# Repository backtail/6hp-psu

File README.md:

# 6hp psu
6HP Eurorack module

### Render

### Input
- 15V-20V
- 2.1/5.5mm Barrel Jack 
- use a *USB PD Trigger Adapter* i.e. to use a power bank

### Output
Without a heatsink
* +5V @ 1.5A
* +12V @ 1A
* -12V @ 1A

Not tested with a heatsink yet. Potentially up to 2..2.5A
per rail! *(Depending on heatsink dimensions and rack depth)*

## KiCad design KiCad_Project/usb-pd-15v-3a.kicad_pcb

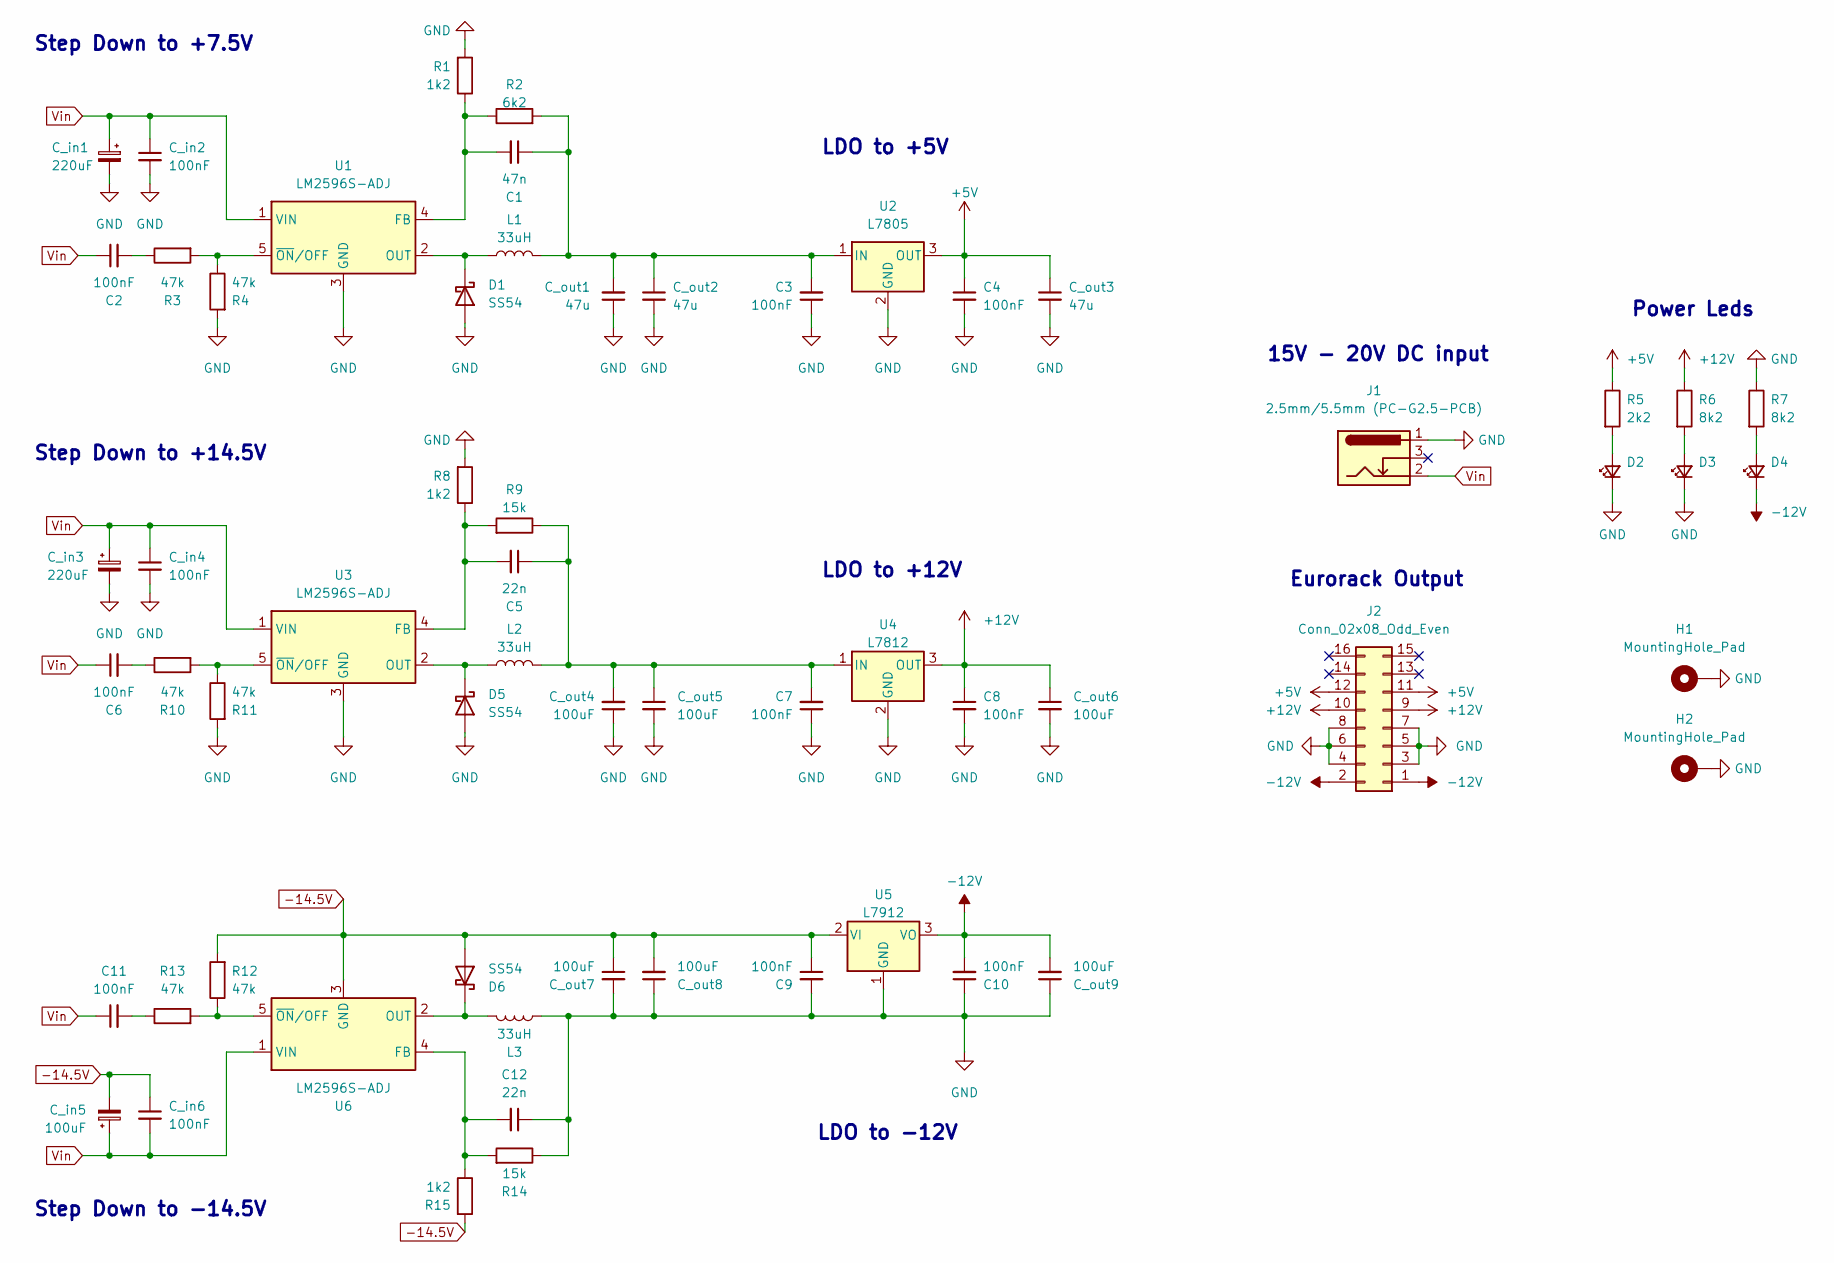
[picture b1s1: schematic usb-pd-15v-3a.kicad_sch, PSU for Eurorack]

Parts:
C1: 47n; C_0603_1608Metric; JLCPCB Reference C1622
C2, C3, C4, C6, C7, C8, C9, C10, C11: 100nF; C_0805_2012Metric; JLCPCB Reference C49678
C5, C12: 22n; C_0603_1608Metric; JLCPCB Reference C21122
C_in1, C_in3: 220uF; CP_Elec_10x7.7; JLCPCB Reference C249881
C_in2, C_in4, C_in6: 100nF; C_1206_3216Metric; JLCPCB Reference C24497
C_in5: 100uF; CP_Elec_6.3x7.7; JLCPCB Reference C165974
C_out1, C_out2, C_out3: 47u; C_1206_3216Metric; JLCPCB Reference C96123
C_out4, C_out5, C_out6, C_out7, C_out8, C_out9: 100uF; L_1210_3225Metric; JLCPCB Reference C90143
D1, D5, D6: SS54; D_SMA; JLCPCB Reference C22452
D2, D3, D4: LED_D3.0mm
H1, H2: MountingHole_Pad; MountingHole_3.2mm_M3_Pad_TopOnly
J1: 2.5mm/5.5mm (PC-G2.5-PCB); DC_Barrel_Jack_2.5mm_5.7mm_Verrtical
J2: Conn_02x08_Odd_Even; IDC-Header_2x08_P2.54mm_Vertical
L1, L2, L3: 33uH; L_12x12mm_H8mm; JLCPCB Reference C718306
R1, R8, R15: 1k2; R_0805_2012Metric_Pad1.20x1.40mm_HandSolder; JLCPCB Reference C17379
R2: 6k2; R_0805_2012Metric_Pad1.20x1.40mm_HandSolder; JLCPCB Reference C17767
R3, R4, R10, R11, R12, R13: 47k; R_0603_1608Metric; JLCPCB Reference C25819
R5: 2k2; R_0603_1608Metric; JLCPCB Reference C4190
R6, R7: 8k2; R_0603_1608Metric; JLCPCB Reference C25981
R9, R14: 15k; R_0805_2012Metric_Pad1.20x1.40mm_HandSolder; JLCPCB Reference C17475
U1, U3, U6: LM2596S-ADJ; TO-263-5_TabPin3; JLCPCB Reference C347423
U2: L7805; TO-263-3_TabPin2; JLCPCB Reference C507146
U4: L7812; TO-263-3_TabPin2; JLCPCB Reference C507140
U5: L7912; TO-263-3_TabPin2; JLCPCB Reference C2926383

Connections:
+5V: C4.1, C_out3.1, J2.11, J2.12, R5.1, U2.3 (OUT)
+12V: C8.1, C_out6.1, J2.9, J2.10, R6.1, U4.3 (OUT)
-12V: C10.2, C_out9.2, D4.1 (K), J2.1, J2.2, U5.3 (VO)
-14.5V: C9.1, C_in5.2, C_in6.1, C_out7.1, C_out8.2, D6.2 (A), R12.2, R15.2, U5.2 (VI), U6.3 (GND)
GND: C3.1, C4.2, C7.1, C8.2, C9.2, C10.1, C12.1, C_in1.2, C_in2.2, C_in3.2, C_in4.2, C_out1.1, C_out2.2, C_out3.2, C_out4.1, C_out5.2, C_out6.2, C_out7.2, C_out8.1, C_out9.1, D1.2 (A), D2.1 (K), D3.1 (K), D5.2 (A), H1.1, H2.1, J1.1, J2.3, J2.4, J2.5, J2.6, J2.7, J2.8, L3.1, R1.2, R4.2, R7.1, R8.2, R11.2, R14.1, U1.3 (GND), U2.2 (GND), U3.3 (GND), U4.2 (GND), U5.1 (GND)
unnamed: C1.1, C3.2, C_out1.2, C_out2.1, L1.2, R2.2, U2.1 (IN)
unnamed: C1.2, R1.1, R2.1, U1.4 (FB)
unnamed: C2.2, R3.1
unnamed: C5.1, C7.2, C_out4.2, C_out5.1, L2.2, R9.1, U4.1 (IN)
unnamed: C5.2, R8.1, R9.2, U3.4 (FB)
unnamed: C6.2, R10.1
unnamed: C11.2, R13.1
unnamed: C12.2, R14.2, R15.1, U6.4 (FB)
unnamed: D1.1 (K), L1.1, U1.2 (OUT)
unnamed: D2.2 (A), R5.2
unnamed: D3.2 (A), R6.2
unnamed: D4.2 (A), R7.2
unnamed: D5.1 (K), L2.1, U3.2 (OUT)
unnamed: D6.1 (K), L3.2, U6.2 (OUT)
unnamed: R3.2, R4.1, U1.5 (~ON/OFF)
unnamed: R10.2, R11.1, U3.5 (~ON/OFF)
unnamed: R12.1, R13.2, U6.5 (~ON/OFF)
Vin: C2.1, C6.1, C11.1, C_in1.1, C_in2.1, C_in3.1, C_in4.1, C_in5.1, C_in6.2, J1.2, U1.1 (VIN), U3.1 (VIN), U6.1 (VIN)

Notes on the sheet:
LDO to -12V
LDO to +12V
Eurorack Output
Power Leds
Step Down to +14.5V
15V - 20V DC input
Step Down to +7.5V
Step Down to -14.5V
LDO to +5V

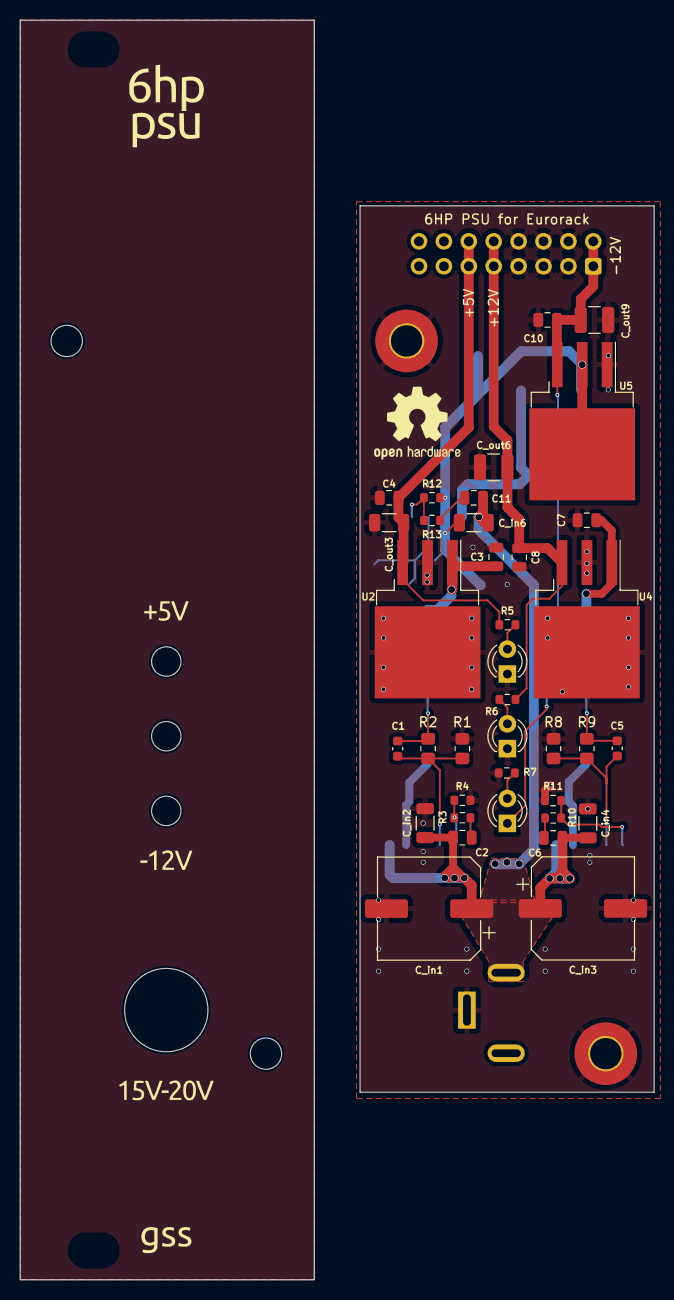
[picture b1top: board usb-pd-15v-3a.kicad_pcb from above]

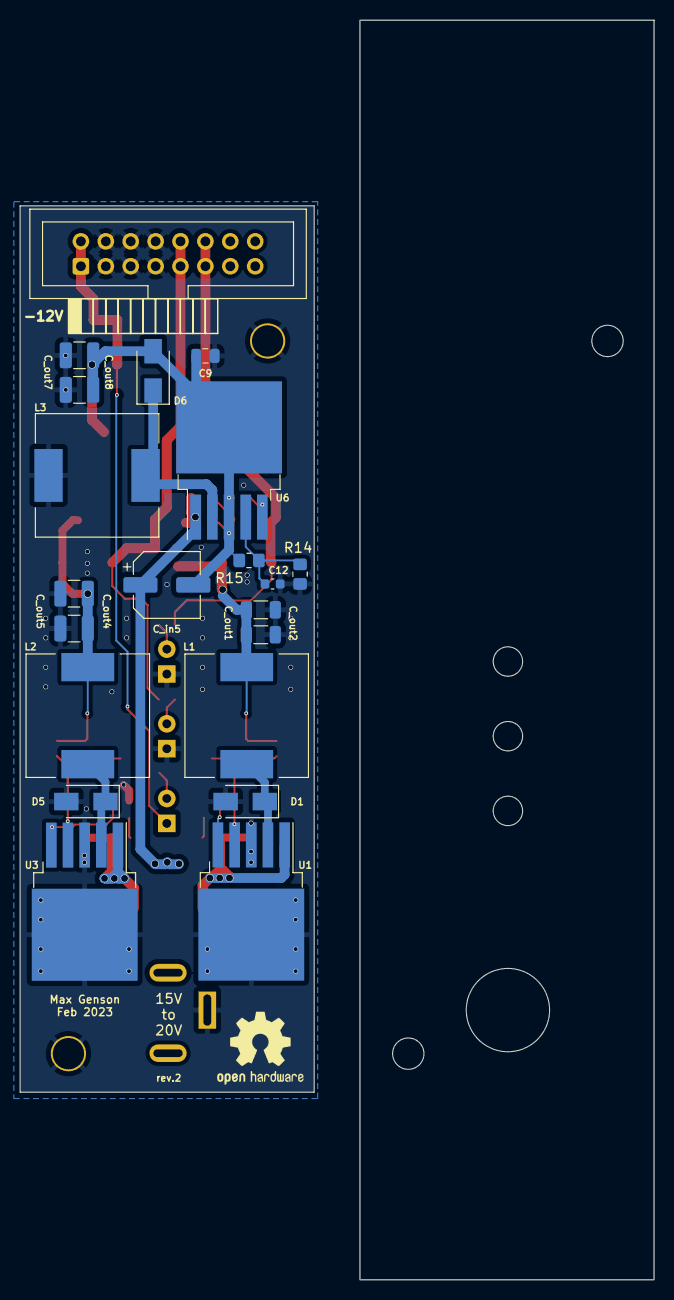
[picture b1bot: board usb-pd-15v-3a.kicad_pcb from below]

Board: 4 copper layers, 64.7 x 128.5 mm, 61 parts (21 on the bottom side), 23 nets.

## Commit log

2024-10-23 update psu git
